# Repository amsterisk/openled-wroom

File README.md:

# OpenLED WROOM host board

An open-hardware LED controller board for an ESP32-WROOM-32E module running
[WLED](https://kno.wled.ge). It has 5 V in and four level-shifted WS2812B data outputs.

Status: **work in progress**. The schematic is done (ERC clean) and the PCB is routed (DRC clean).
It has not yet been reviewed or fabricated.

## Features

- **ESP32-WROOM-32E** module. The antenna overhangs the top edge of the board, so there is no copper under it.
- **Four WS2812B outputs** on GPIO16, 17, 18 and 19:
  - Buffered to 5 V by a **74AHCT125**. Its TTL-threshold inputs are driven from 3.3 V.
  - A 220 Ω series resistor on each output.
  - A 10 kΩ pull-down on each output, so the strips stay dark while the ESP32 boots.
- **Capacity:** four outputs drive about 1440 LEDs at around 80 fps, for example 24 m of 60 LED/m
  strip split across them. A single 1440-LED output would only reach about 23 fps.
- **5 V input for logic only** (about 0.3 A peak):
  - Reverse-polarity protection (AO3401A P-FET).
  - SMBJ5.0A TVS.
  - AMS1117-3.3 regulator.
- **Button on GPIO0**. This is WLED's default button: tap for on/off, long-press to reset to AP mode.
  Holding it during reset enters download mode.
- **No USB on board.** Flash the module before assembly or through the optional serial header (J6). After that, update over Wi-Fi (WLED OTA).
- 2-layer board, 54 × 39 mm, with two M3 mounting holes.

## Connectors

All connectors are 2-pin JST XH (2.5 mm pitch, vertical, B2B-XH-A). Pin 1 is the signal and pin 2 is GND.

| Ref | Pin 1 | Pin 2 |
|---|---|---|
| J1 | +5 V in | GND |
| J2–J5 | LED data D1–D4 | GND |

Each output has its own connector, so you only need to fit the outputs you use. Fit at least J2
(D1), and set WLED to match.

Each output's GND pin is the data ground reference. **LED power does not go through this board.**
Wire the strip power straight from the PSU(s):
- Inject power about every 150–200 LEDs, with heavy wire and a fuse on each run.
- Join each strip's GND to its output's GND pin.
- Keep the data run from the board to the first LED short (under a few metres).

The data ground wires run in parallel with the heavy power returns. Keep the board near where the
strips are fed, so only a small share of the LED current flows back through it. XH pins are rated
about 3 A.

At full white, 1440 LEDs can draw about 86 A. Set WLED's brightness limiter to about 80 % of what
your supplies can deliver.

## Serial header (optional)

J6 is a 1×4 2.54 mm header for an off-board USB-serial adapter (CH340, CH343, CP2102 and similar).
It's left unfitted by default.

| J6 pin | Signal | Adapter pin |
|---|---|---|
| 1 (square pad) | GND | GND |
| 2 | TX (ESP32 TXD0) | RX |
| 3 | RX (ESP32 RXD0) | TX |
| 4 | EN (reset, active low) | – |

- **Use a 3.3 V adapter**, or set the adapter's jumper to 3.3 V. The ESP32's RX pin isn't 5 V tolerant.
- **No power pin.** Power the board from J1 as usual.
- **To enter download mode:** hold the button (GPIO0), briefly short EN to GND (or power-cycle
  J1), then release the button. Then flash with esptool or the WLED web installer.
- The serial port also carries the ESP32 boot log, at 115200 baud.

## WLED settings

- **LED Preferences:** four outputs, type WS281x, data GPIO **16, 17, 18, 19** (D1–D4).
- **Button 0:** GPIO0, type Pushbutton.
- **Brightness limiter:** on, sized to your PSU(s).

## Building fabrication files

```sh
tools/export.sh            # version from `git describe`; refuses to build if ERC/DRC fail
tools/export.sh v1.0       # explicit version
tools/export.sh --allow-violations   # work-in-progress builds
```

Outputs land in `production/<version>/`. That folder is git-ignored; attach its contents to a
GitHub release. It contains:
- A Gerber + drill zip. Upload it as-is to JLCPCB or PCBWay.
- A grouped BOM, plus a JLCPCB-format BOM and placement file.
- The schematic PDF and top/bottom 3D renders.
- The ERC/DRC reports.

You need KiCad 9 (`kicad-cli`).

Design rules target JLCPCB's standard 2-layer process. They are set in Board Setup → Constraints
plus `hardware/openled-wroom.kicad_dru`:
- 0.15 mm minimum track width and clearance.
- **All vias 0.6/0.3 mm or larger**, so the board needs no small-via surcharge.
- 0.3 mm copper-to-edge.

Net classes:
- *Default:* 0.25 mm tracks.
- *Power:* 0.5 mm tracks and 0.8/0.4 mm vias, for +5V, +3V3, GND and VIN.

## Repository layout

- `hardware/`: the KiCad 9 project (`openled-wroom.kicad_pro`).
  - `openled.pretty/ESP32-WROOM-32E` is KiCad's stock footprint with two changes: its
    exposed-pad thermal vias are opened from 0.2 to 0.3 mm, and the pin-1 marker is moved onto the board.
  - `openled.pretty/amsterisk-logo` is the silkscreen logo.
- `tools/export.sh`: builds the fabrication and documentation outputs.
- `LICENSE`: CERN-OHL-S-2.0.

## Licence

Copyright the contributors. Licensed under the **CERN Open Hardware Licence Version 2 –
Strongly Reciprocal** (CERN-OHL-S-2.0). See `LICENSE`.

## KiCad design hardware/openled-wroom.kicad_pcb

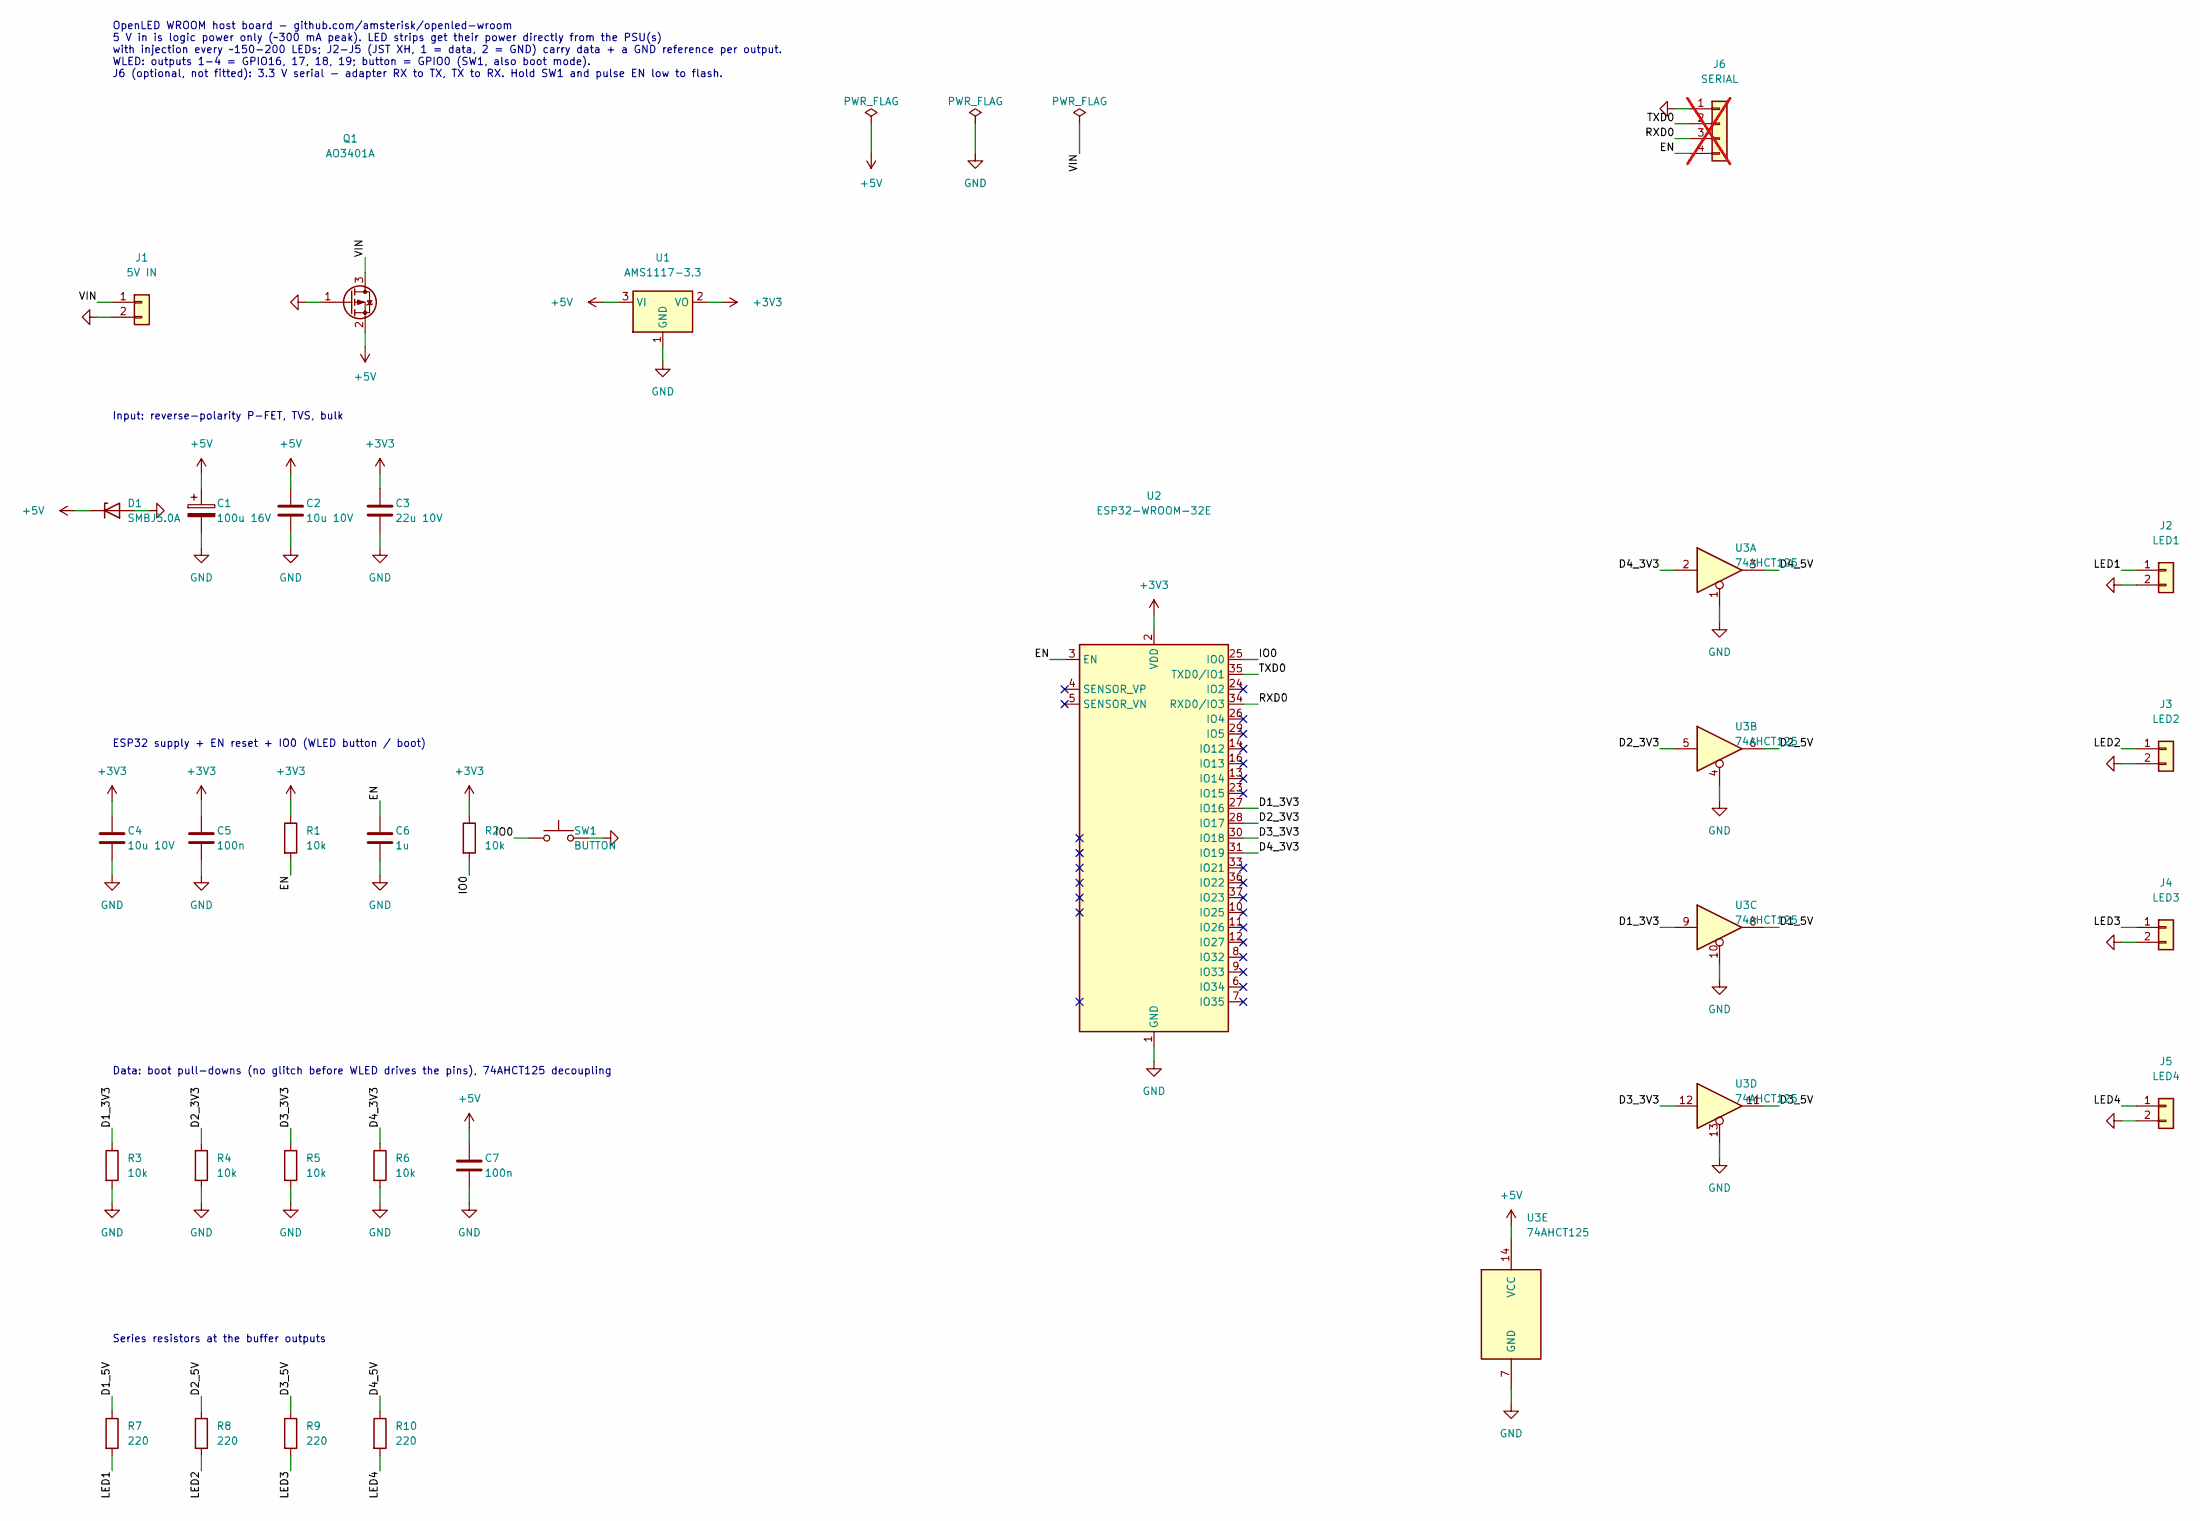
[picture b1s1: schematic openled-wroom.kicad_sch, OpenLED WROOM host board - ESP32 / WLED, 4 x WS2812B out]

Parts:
C1: 100u 16V; CP_Elec_6.3x5.8
C2, C4: 10u 10V; C_0805_2012Metric
C3: 22u 10V; C_1206_3216Metric
C5, C7: 100n; C_0603_1608Metric
C6: 1u; C_0603_1608Metric
D1: SMBJ5.0A; D_SMB
J1: 5V IN; JST_XH_B2B-XH-A_1x02_P2.50mm_Vertical
J2: LED1; JST_XH_B2B-XH-A_1x02_P2.50mm_Vertical
J3: LED2; JST_XH_B2B-XH-A_1x02_P2.50mm_Vertical
J4: LED3; JST_XH_B2B-XH-A_1x02_P2.50mm_Vertical
J5: LED4; JST_XH_B2B-XH-A_1x02_P2.50mm_Vertical
J6: SERIAL; PinHeader_1x04_P2.54mm_Vertical; not fitted
Q1: AO3401A; SOT-23
R1, R2, R3, R4, R5, R6: 10k; R_0603_1608Metric
R7, R8, R9, R10: 220; R_0603_1608Metric
SW1: BUTTON; SW_SPST_PTS645Sx43SMTR92
U1: AMS1117-3.3; SOT-223-3_TabPin2
U2: ESP32-WROOM-32E
U3: 74AHCT125; SOIC-14_3.9x8.7mm_P1.27mm

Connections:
+3V3: C3.1, C4.1, C5.1, R1.1, R2.1, U1.2 (VO), U2.2 (VDD)
+5V: C1.1, C2.1, C7.1, D1.1 (K), Q1.2 (S), U1.3 (VI), U3.14 (VCC)
/D1_3V3: R3.1, U2.27 (IO16), U3.9
/D1_5V: R7.1, U3.8
/D2_3V3: R4.1, U2.28 (IO17), U3.5
/D2_5V: R8.1, U3.6
/D3_3V3: R5.1, U2.30 (IO18), U3.12
/D3_5V: R9.1, U3.11
/D4_3V3: R6.1, U2.31 (IO19), U3.2
/D4_5V: R10.1, U3.3
/EN: C6.1, J6.4, R1.2, U2.3 (EN)
/IO0: R2.2, SW1.1, U2.25 (IO0)
/LED1: J2.1, R7.2
/LED2: J3.1, R8.2
/LED3: J4.1, R9.2
/LED4: J5.1, R10.2
/RXD0: J6.3, U2.34 (RXD0/IO3)
/TXD0: J6.2, U2.35 (TXD0/IO1)
/VIN: J1.1, Q1.3 (D)
GND: C1.2, C2.2, C3.2, C4.2, C5.2, C6.2, C7.2, D1.2 (A), J1.2, J2.2, J3.2, J4.2, J5.2, J6.1, Q1.1 (G), R3.2, R4.2, R5.2, R6.2, SW1.2, U1.1 (GND), U2.1 (GND), U2.15 (GND), U2.38 (GND), U2.39 (GND), U3.1, U3.4, U3.7 (GND), U3.10, U3.13

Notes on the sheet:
Input: reverse-polarity P-FET, TVS, bulk
ESP32 supply + EN reset + IO0 (WLED button / boot)
Data: boot pull-downs (no glitch before WLED drives the pins), 74AHCT125 decoupling
Series resistors at the buffer outputs
OpenLED WROOM host board - github.com/amsterisk/openled-wroom 5 V in is logic power only (~300 mA peak). LED strips get their power directly from the PSU(s) with injection every ~150-200 LEDs; J2-J5 (JST XH, 1 = data, 2 = GND) carry data + a GND reference per output. WLED: outputs 1-4 = GPIO16, 17,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

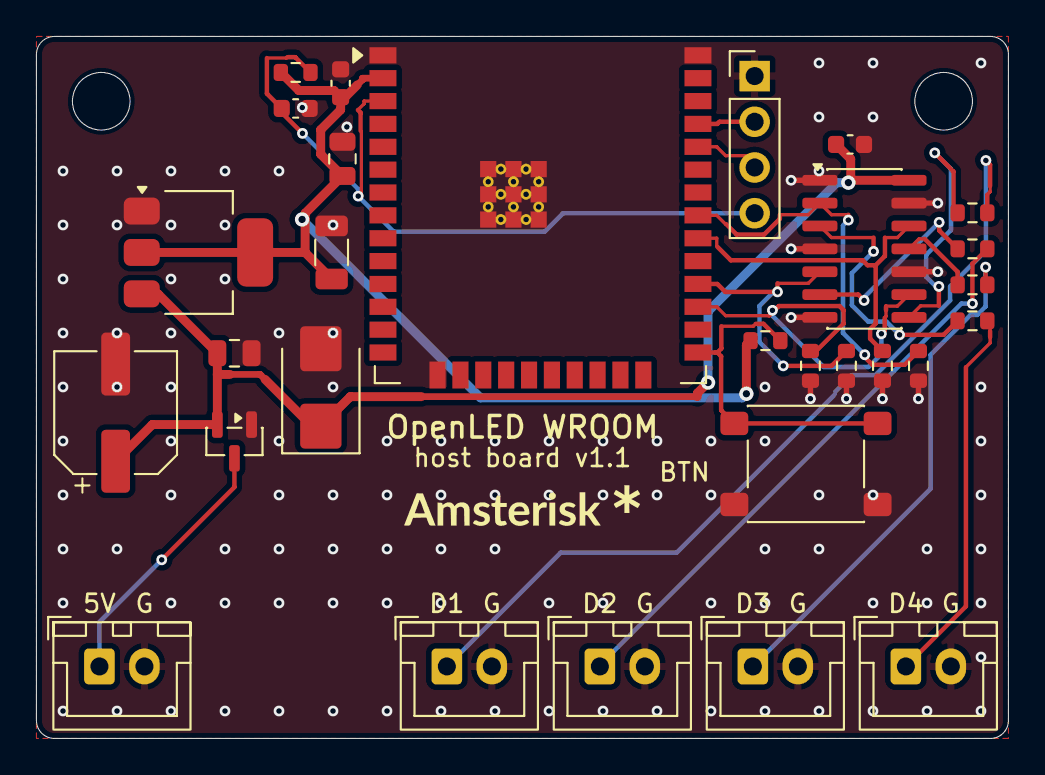
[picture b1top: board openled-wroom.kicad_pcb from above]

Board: 2 copper layers, 54.0 x 39.0 mm, 33 parts (1 on the bottom side), 20 nets.

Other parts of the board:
H1, H2: MountingHole_3.2mm_M3
LOGO1: LOGO; amsterisk-logo
LOGO2: OSHW-Logo2_7.3x6mm_SilkScreen
